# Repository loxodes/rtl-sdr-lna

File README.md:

**rtl-sdr-lna**

rtl-sdr-lna is a LNA for the ezcap digital TV USB stick (or other USB tuners).
This is intended to improve the sensitivity of it for use as a cheap SDR.

The amplifier is stable, but the matching could probably be improved.

See the following websites for more information on the rtl-sdr:

http://sdr.osmocom.org/trac/wiki/rtl-sdr

http://www.reddit.com/r/rtlsdr

The board is intended to take the place of the RF connector on the ezcap.  

s2p files for simulation are available from Avago and Murata. I'm using ADS for simulation, qucs would be a free open source alternative.

http://www.avagotech.com/pages/en/rf_microwave/amplifiers/low_noise_amplifiers/mga-62563/

http://ds.murata.co.jp/software/simsurfing/en-us/index.html

The PCB can be ordered from OSH Park for $3.15 here: http://oshpark.com/shared_projects/ExVzBewI

All layouts and schematics in this repository are under an MIT license.
Feel free to contact me at jtklein@alaska.edu with suggestions, questions, or complaints.

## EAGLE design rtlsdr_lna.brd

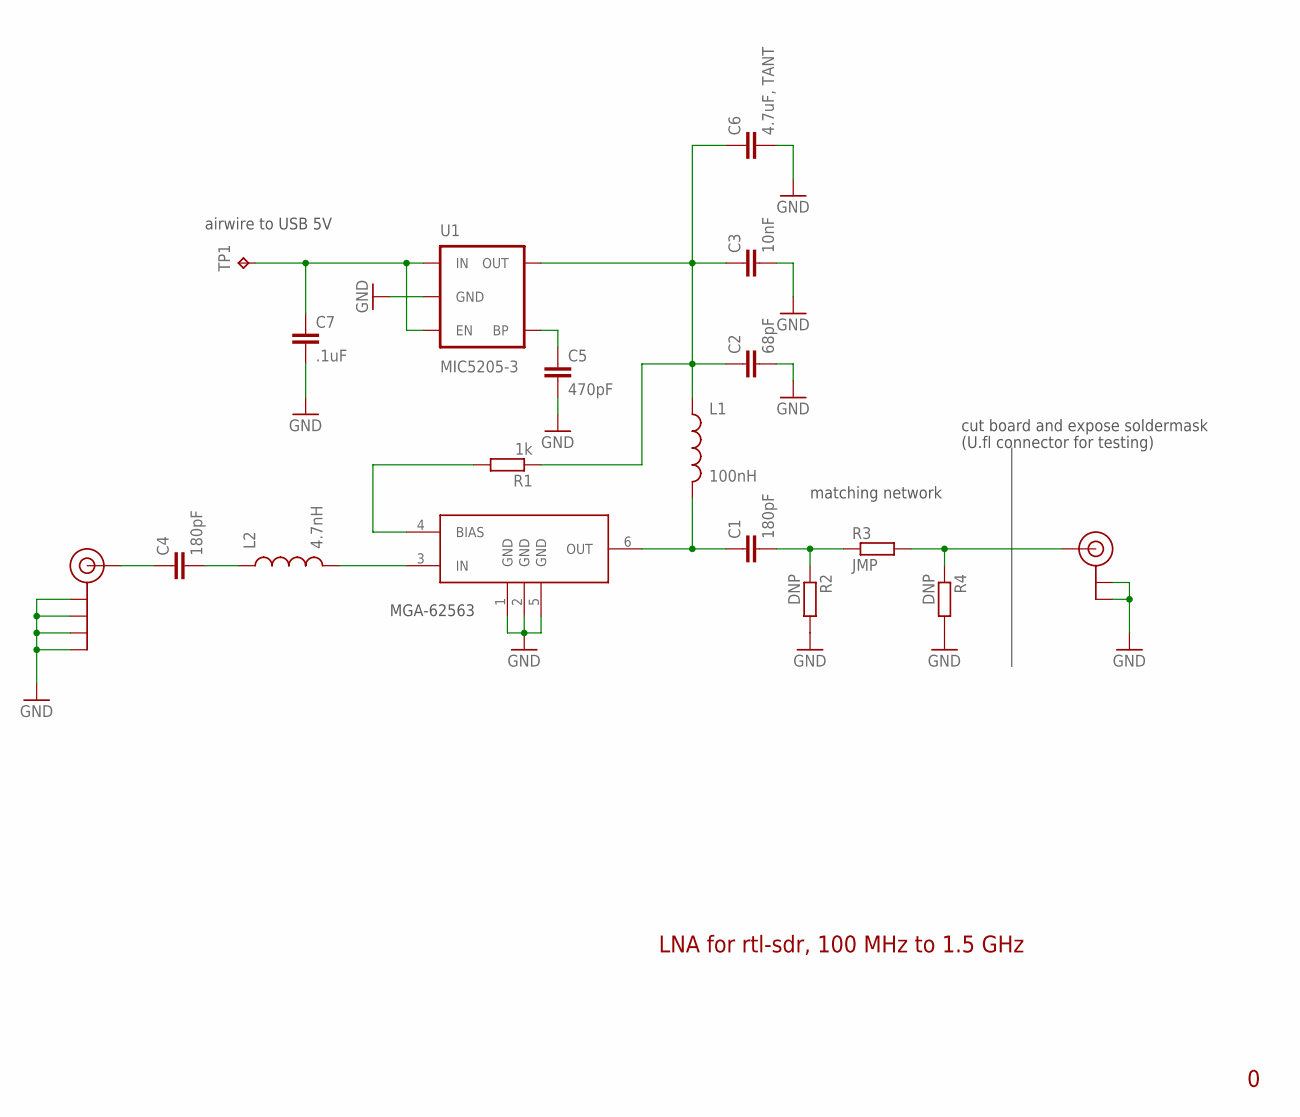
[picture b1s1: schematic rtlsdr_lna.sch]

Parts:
C1, C4: 180pF; C0402
C2: 68pF; C0402
C3: 10nF; C0402
C5: 470pF; C0402
C6: 4.7uF, TANT; C0805
C7: .1uF; C0603
J$1: SMA_EDGE; SMA-EDGE
L1: 100nH; 0603
L2: 4.7nH; C0402
R1: 1k; R0402
R2, R4: DNP; R0402
R3: JMP; R0402
TP1: TPTP20SQ; TP20SQ
U1: MIC5205-3; SOT23-5
U$1: MGA-68563; SOT363
U$2: U.FL

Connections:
GND: C2.2, C3.2, C5.2, C6.2, C7.2, J$1.GND@0 (GND), J$1.GND@1 (GND), J$1.GND@2 (GND), J$1.GND@3 (GND), R2.2, R4.2, U1.2 (GND), U$1.1 (GND), U$1.2 (GND), U$1.5 (GND), U$2.P$1 (GND), U$2.P$2 (GND)
unnamed: R1.2, U$1.4 (BIAS)
unnamed: C1.2, R2.1, R3.1
unnamed: C1.1, L1.2, U$1.6 (OUT)
unnamed: R3.2, R4.1, U$2.P$3 (SIGNAL)
unnamed: C2.1, C3.1, C6.1, L1.1, R1.1, U1.5 (OUT)
unnamed: C5.1, U1.4 (BP)
unnamed: C7.1, TP1.TP, U1.1 (IN), U1.3 (EN)
unnamed: C4.1, J$1.SIG (SIGNAL)
unnamed: C4.2, L2.1
unnamed: L2.2, U$1.3 (IN)

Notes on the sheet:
matching network
cut board and expose soldermask
(U.fl connector for testing)
airwire to USB 5V
MGA-62563
LNA for rtl-sdr, 100 MHz to 1.5 GHz

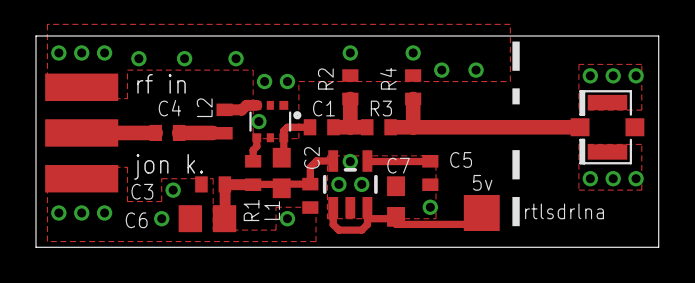
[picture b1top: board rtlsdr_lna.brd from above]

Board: 2 copper layers, 34.6 x 11.7 mm, 18 parts (0 on the bottom side), 11 nets.

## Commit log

2012-03-20 initial (untested) commit
2012-03-20 increased inductor package size, added missing ldo and rbias component values
2012-03-21 added s paramters from avago and murata for simulation
2012-03-21 added s paramters from avago and murata for simulation.. ending in S2P
2012-03-21 changed values in matching network for improved S11 at lower frequencies (increased DC bias inductor value, increased DC blocking capacitor values to 330pF)
2012-03-21 reduced board size, increased clearances, changed voltage regulator footprint, added silkscreen and annotations
2012-03-21 moved images to kl1xf.org
2012-03-21 updated README.md with new links
2012-03-21 noise.. updated README.md to fix header formatting
2012-03-21 changed amplifier to MGA-62563, changed bias network for better return loss
2012-03-21 this time with the new layout and schematic..
2012-03-21 unbroke README.md
2012-03-22 cleaned up layout to pass DRC, rtl-sdr-lna ready for manufacturing
2012-04-26 added s2p measurements
2012-04-26 added RTLSDRLNA picture
2012-10-19 moved images of board and schematic to github (fixed broken links to images in the README file)
2013-09-12 cleaned up silkscreen layer, added bom, added link of where to order the pcbs
2016-04-27 Updated contact email.

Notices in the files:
parts and their libraries:
SparkFun-PowerIC: Licensing: CC v3.0 Share-Alike You are welcome to use this library for commercial purposes.
